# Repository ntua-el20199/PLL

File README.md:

# PLL (Phase-Locked Loop) Project

This project encompasses the design, simulation, and documentation of a Phase-Locked Loop (PLL) circuit. It includes PCB layouts created with KiCad and circuit simulations performed with LTSpice.

## Project Structure

The repository is organized as follows:

*   **`PCB/`**: Contains all KiCad project files related to the Printed Circuit Board (PCB) design of the PLL.
    *   **`PCB/prototype/`**: KiCad project files for a prototype version of the PLL PCB.
    *   **`PCB/testing/`**: KiCad project files used for testing purposes.
    *   **`PCB/simulator_kicad/`**: KiCad projects tailored for circuit simulation, integrating SPICE models.

*   **`simulations/`**: Contains LTSpice simulation files and related documentation.
    *   **`simulations/final.asc`**: An LTSpice simulation schematic.
    *   **`simulations/pll.asc`**: The primary LTSpice simulation schematic for the PLL.
    *   **`simulations/small_signal.asc`**: An LTSpice schematic of the PLL as a system for small-signal behavior analysis.
    *   **`simulations/simulation_log/`**: LaTeX source files for the simulation report.

*   **`report.pdf`**: An overview of the theory behind PLLs and our specific implementation.

## Software & Tools

*   **PCB Design**: KiCad EDA Suite
*   **Circuit Simulation**: LTSpice

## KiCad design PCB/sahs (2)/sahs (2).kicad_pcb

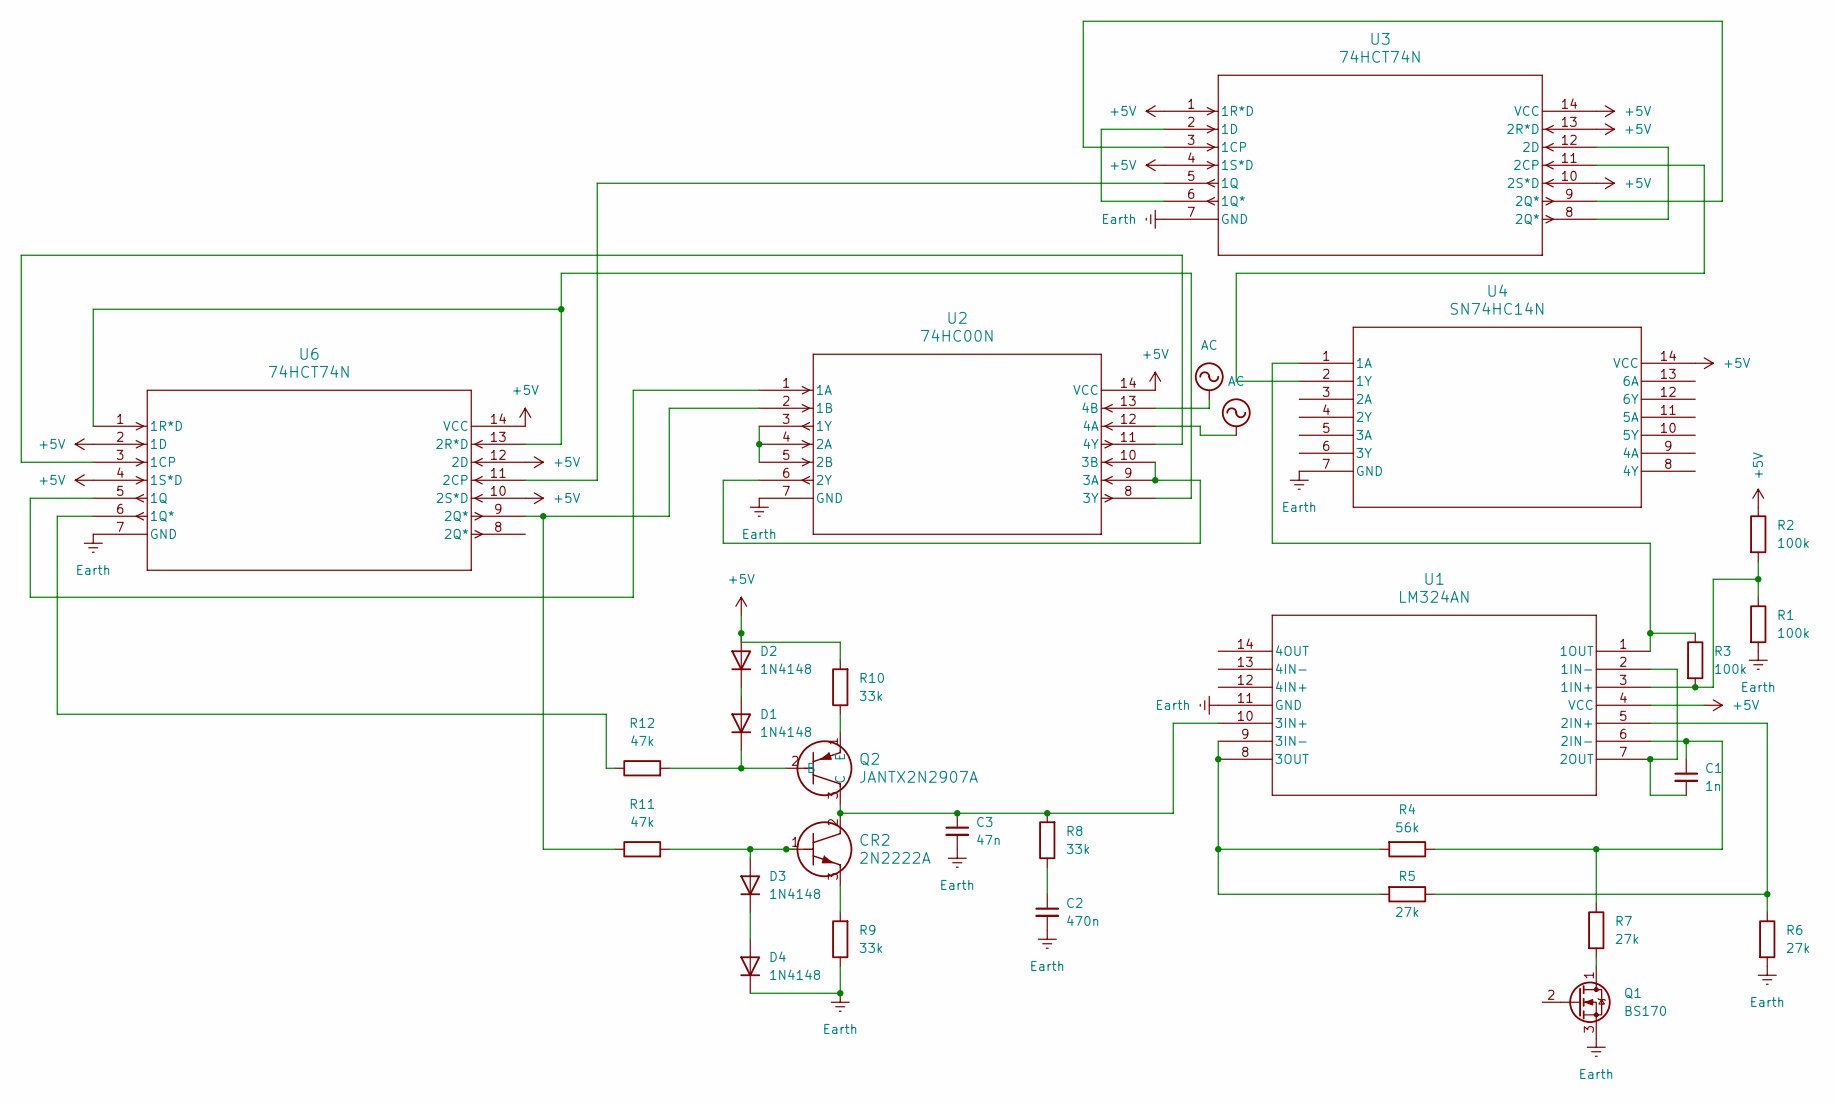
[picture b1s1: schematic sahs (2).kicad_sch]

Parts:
C1: 1n; C_Disc_D3.0mm_W1.6mm_P2.50mm
C2: 470n; C_Rect_L7.0mm_W6.0mm_P5.00mm
C3: 47n; C_Disc_D3.0mm_W1.6mm_P2.50mm
CR2: 2N2222A; TO-18_STM
D1, D2, D3, D4: 1N4148; D_DO-35_SOD27_P7.62mm_Horizontal
Q1: BS170; TO-92_Inline
Q2: JANTX2N2907A; TO-18TO-206AA_MCH
R1, R2, R3: 100k; R_Axial_DIN0207_L6.3mm_D2.5mm_P7.62mm_Horizontal
R4: 56k; R_Axial_DIN0207_L6.3mm_D2.5mm_P7.62mm_Horizontal
R5, R6, R7: 27k; R_Axial_DIN0207_L6.3mm_D2.5mm_P7.62mm_Horizontal
R8, R9, R10: 33k; R_Axial_DIN0207_L6.3mm_D2.5mm_P7.62mm_Horizontal
R11, R12: 47k; R_Axial_DIN0207_L6.3mm_D2.5mm_P7.62mm_Horizontal
U1: LM324AN; N14
U2: 74HC00N; SOT27-1_NEX
U3, U6: 74HCT74N; SOT27-1_NEX
U4: SN74HC14N; N14

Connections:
+5V: D2.2 (A), R2.1, R10.2, U1.4 (VCC), U2.14 (VCC), U3.1 (1R*D), U3.4 (1S*D), U3.10 (2S*D), U3.13 (2R*D), U3.14 (VCC), U4.14 (VCC), U6.2 (1D), U6.4 (1S*D), U6.10 (2S*D), U6.12 (2D), U6.14 (VCC)
AC: U2.12 (4A), U2.13 (4B)
Earth: C2.2, C3.2, D4.1 (K), Q1.3 (S), R1.2, R6.2, R9.1, U1.11 (GND), U2.7 (GND), U3.7 (GND), U4.7 (GND), U6.7 (GND)
unnamed: C2.1, R8.1
unnamed: CR2.3, R9.2
unnamed: D1.2 (A), D2.1 (K)
unnamed: D1.1 (K), Q2.2 (B), R12.2
unnamed: CR2.1, D3.2 (A), R11.2
unnamed: D3.1 (K), D4.2 (A)
unnamed: Q1.1 (D), R7.2
unnamed: C3.1, CR2.2, Q2.3 (C), R8.2, U1.10 (3IN+)
unnamed: Q2.1 (E), R10.1
unnamed: R1.1, R2.2, R3.2, U1.3 (1IN+)
unnamed: C1.2, U1.2 (1IN-), U1.7 (2OUT)
unnamed: R3.1, U1.1 (1OUT), U4.1 (1A)
unnamed: R5.1, R6.1, U1.5 (2IN+)
unnamed: C1.1, R4.1, R7.1, U1.6 (2IN-)
unnamed: R4.2, R5.2, U1.8 (3OUT), U1.9 (3IN-)
unnamed: U2.1 (1A), U6.5 (1Q)
unnamed: R11.1, U2.2 (1B), U6.9 (2Q*)
unnamed: U2.3 (1Y), U2.4 (2A), U2.5 (2B)
unnamed: U2.6 (2Y), U2.9 (3A), U2.10 (3B)
unnamed: U2.8 (3Y), U6.1 (1R*D), U6.13 (2R*D)
unnamed: U2.11 (4Y), U6.3 (1CP)
unnamed: U3.3 (1CP), U3.9 (2Q*)
unnamed: U3.2 (1D), U3.6 (1Q*)
unnamed: U3.5 (1Q), U6.11 (2CP)
unnamed: U3.11 (2CP), U4.2 (1Y)
unnamed: U3.8 (2Q*), U3.12 (2D)
unnamed: R12.1, U6.6 (1Q*)

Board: 2 copper layers, 27 parts (0 on the bottom side), 30 nets, no tracks yet.

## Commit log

2025-05-11 add README
2025-05-11 minor change
2025-05-11 add image
2025-05-12 add vco simulation
2025-05-12 vco parametric simulation
2025-05-12 backup parametric log
2025-05-13 add 3 state switch to pll
2025-05-14 change vco topology
2025-05-14 update pll
